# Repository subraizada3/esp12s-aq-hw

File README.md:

# ESP8266-based air quality sensor master board

This is a board that powers an ESP-12S module with USB-C, and has breakouts for I2C and UART.

Designed for use as an air quality sensor in combination with:

- Sensirion SCD41 (high accuracy NDIR CO2) - available on an I2C breakout board from various manufacturers
- Sensirion SGP40 (VOC) - available on an I2C breakout board from various manufacturers
- Sensirion SPS30 (particulate matter) - Sensirion manufactures an eval kit that comes with a cable, Sparkfun also sells their own similar kit

Though there's nothing really air-quality-specific here. This is a generic board that powers an ESP-12S and breaks out the I2C/UART pins + 5v/3.3v power to headers. Whatever you connect to those headers is up to you.

See [bom.ods](./bom.ods) for LCSC part numbers for this board (for PCB assembly by JLCPCB).

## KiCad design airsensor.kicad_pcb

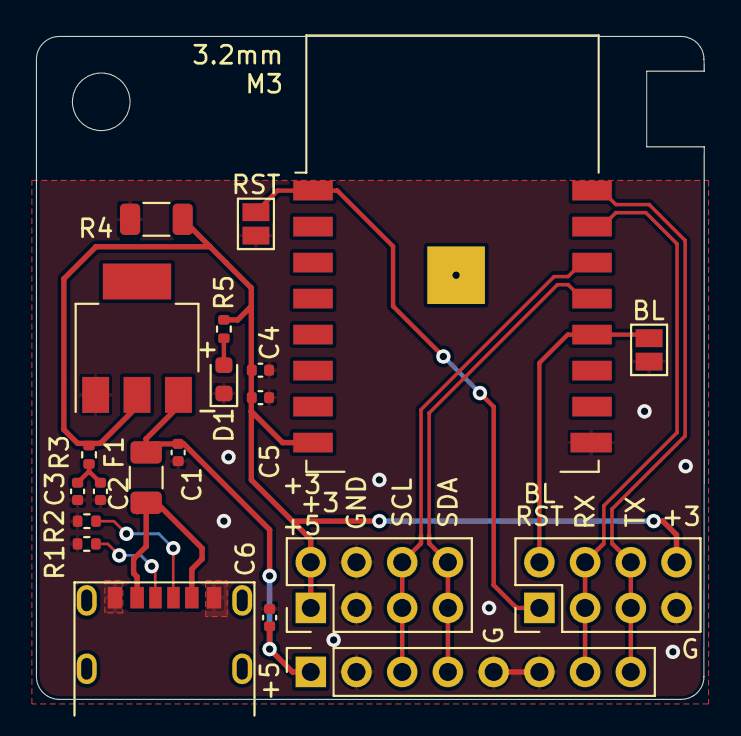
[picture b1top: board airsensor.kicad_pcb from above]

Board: 2 copper layers, 37.1 x 36.8 mm, 22 parts (0 on the bottom side), 14 nets.

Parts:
C1, C6: 1uF; C_0402_1005Metric
C2, C3, C4: 10uF; C_0402_1005Metric
C5: 0.1uF; C_0402_1005Metric
D1: LED; LED_0603_1608Metric
F1: 1A hold; Fuse_1206_3216Metric
H1: M3; MountingHole_3.2mm_M3
J1: USB-C; M17
J2: SCD41 CO2 / SGP40 VOC; PinHeader_2x04_P2.54mm_Vertical
J3: SPS30 PM; PinSocket_1x08_P2.54mm_Vertical
J4: TTL Serial; PinHeader_2x04_P2.54mm_Vertical
JP1: RST; SolderJumper-2_P1.3mm_Open_Pad1.0x1.5mm
JP2: BL; SolderJumper-2_P1.3mm_Open_Pad1.0x1.5mm
R1, R2: 5.1k; R_0402_1005Metric
R3: 1; R_0402_1005Metric
R4: 270-330; R_1206_3216Metric
R5: 1k; R_0402_1005Metric
U1: AMS1117-3.3; SOT-223-3_TabPin2
U2: ESP-12S

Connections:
+3V3: C4.1, C5.1, J2.1, J2.2, J4.8, R3.1, R4.2, R5.2, U1.2, U2.8
+5V: C1.1, C6.2, F1.1, J3.1, U1.3
/DTR: J4.2, JP2.1, U2.12
/RST: J4.1, JP1.1, U2.1
/RX: J3.7, J4.3, J4.4, U2.15
/SCL: J2.5, J2.6, J3.3, U2.14
/SDA: J2.7, J2.8, J3.4, U2.13
/TX: J3.8, J4.5, J4.6, U2.16
GND: C1.2, C2.2, C3.2, C4.2, C5.2, C6.1, D1.1, J1.A12, J2.3, J2.4, J3.2, J3.5, J3.6, J4.7, JP1.2, JP2.2, R1.1, R2.1, R4.1, U1.1, U2.9
unnamed: C2.1, C3.1, R3.2
unnamed: D1.2, R5.1
unnamed: F1.2, J1.B9
unnamed: J1.A5, R1.2
unnamed: J1.B5, R2.2

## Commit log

2024-12-19 track project
